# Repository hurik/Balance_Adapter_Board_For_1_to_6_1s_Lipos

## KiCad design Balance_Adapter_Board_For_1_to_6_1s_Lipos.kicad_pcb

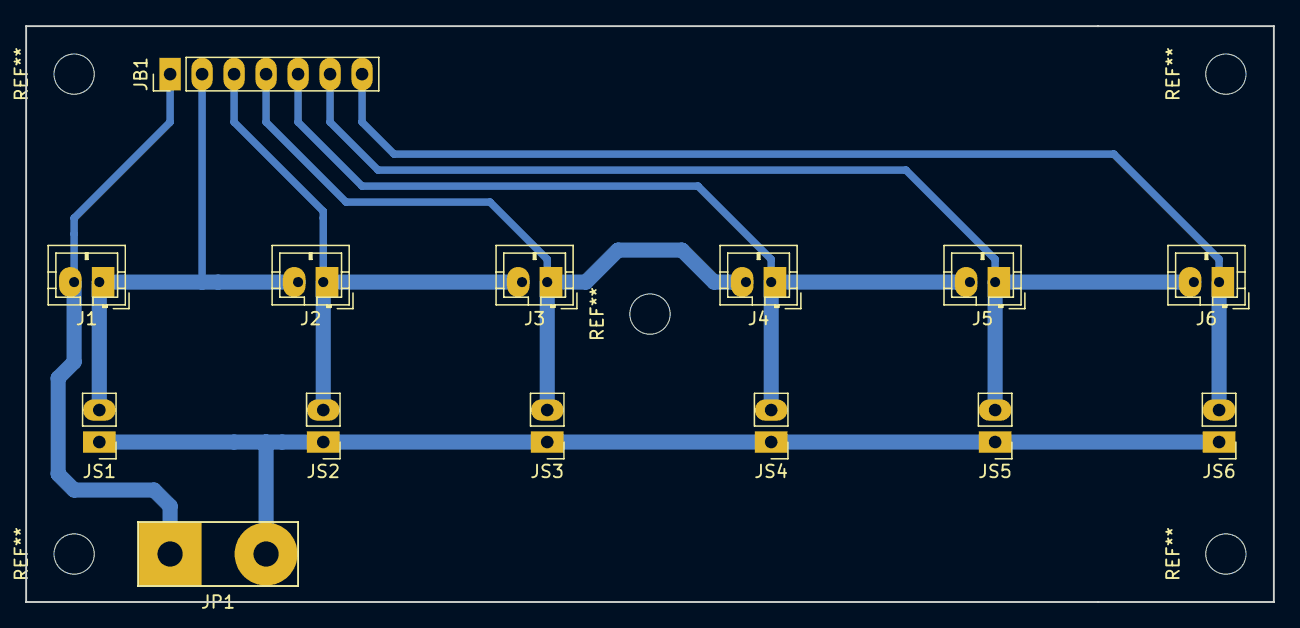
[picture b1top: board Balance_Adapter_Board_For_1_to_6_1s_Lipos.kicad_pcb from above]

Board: 2 copper layers, 99.1 x 45.7 mm, 14 parts (0 on the bottom side), 8 nets.

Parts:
J1, J2, J3, J4, J5, J6: Conn_01x02_Male; JST_PH_B2B-PH-K_1x02_P2.00mm_Vertical
JB1: Conn_01x07_Male; PinHeader_1x07_P2.54mm_Vertical
JP1: Conn_01x02_Male; PowerCable
JS1, JS2, JS3, JS4, JS5, JS6: Conn_01x02; Pin_Header_Straight_1x02_Pitch2.54mm

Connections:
/+: JP1.2, JS1.1, JS2.1, JS3.1, JS4.1, JS5.1, JS6.1
/+1s: J1.1, J2.2, JB1.2, JS1.2
/+2s: J2.1, J3.2, JB1.3, JS2.2
/+3s: J3.1, J4.2, JB1.4, JS3.2
/+4s: J4.1, J5.2, JB1.5, JS4.2
/+5s: J5.1, J6.2, JB1.6, JS5.2
/+6s: J6.1, JB1.7, JS6.2
/-: J1.2, JB1.1, JP1.1

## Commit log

2018-09-30 first version
2018-10-01 improved traces
2018-10-10 replaced switches with pinheader for jumper
2018-10-11 changed big pinheader to seperate ones located at the lipo connectors
2018-10-11 added fifth mounting hole
2018-10-11 added baseplate
2018-10-11 improved pads
2018-10-12 increased baseplate size
2018-10-16 added support for thick wires and some text
2018-10-16 improved power connector and fixed text
